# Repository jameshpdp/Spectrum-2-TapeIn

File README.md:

# ZX Spectrum +2 (Grey) External Tape Input PCB

This is a simple PCB layout for building circuit designed by
[JoulesperCoulomb](https://youtu.be/qUIv-A_DOc0?t=1213), please
watch the video for all the details.

Board size 40mm x 30mm. Gerber files under `export/`, original KiCad project under
`Spectrum+2-TapeIn.KiCad/`.

## Building

Building this circuit shold be straghtforward with one exception. It is recommended to solder wires directly to the PCB1 pads and avoid using pin header there.

NOTE: While PCB1 connector footprint allows for soldering KK 254 / KF 2510  pin header, great care should be taken to solder those correctly. The problem is not the pin header itself, but the cable you need to use to connect it to the main board. Most pre-crimped cables available at the time of writing (2023) are the cross-wired ones (pin 1 to 5, pin 2 to 4, pin 4 to 2, pin 5 to 1). Which means if you do not pay attention you may end up cross-connecting MIC and EAR. At best, nothing will work. At worst, you may damage that precious ULA. Just get the wires with the KK 254 / KF 2510 connector on one end and carefully solder wires according to the skilscreen markings.

[Interactive BOM](https://htmlpreview.github.io/?https://github.com/jameshpdp/Spectrum-2-TapeIn/blob/main/bom/ibom.html)

| Reference         | Item     | Count |
| ----------------- | -------- | ----- |
| C1, C2            | 20 nF    |     2 |
| C3                | 22 uF    |     1 |
| R1-R4, R6, R7, R9 | 100 kOhm |     7 |
| R5                | 470 kOhm |     1 |
| R8                | 68 kOhm  |     1 |
| D2            | 1N5819   |     1 |
| U1                | LM358    |     1 |
| DECK1, PCB1 (opt) | Molex KK-254 AE-6410 | 1 (2) |

Molex KK 254 / KF 2510 connectors optional, required only if you want to avoid cutting/modifing existing tape deck wiring. Otherwise you can simply solder wires to the corresponding pads as marked on the PCB.

## Revision Hisory
Rev. C -- first public release

Rev. D -- KK 254 / 2510 connectors (optional), removed D1, extra details on the silkscreen

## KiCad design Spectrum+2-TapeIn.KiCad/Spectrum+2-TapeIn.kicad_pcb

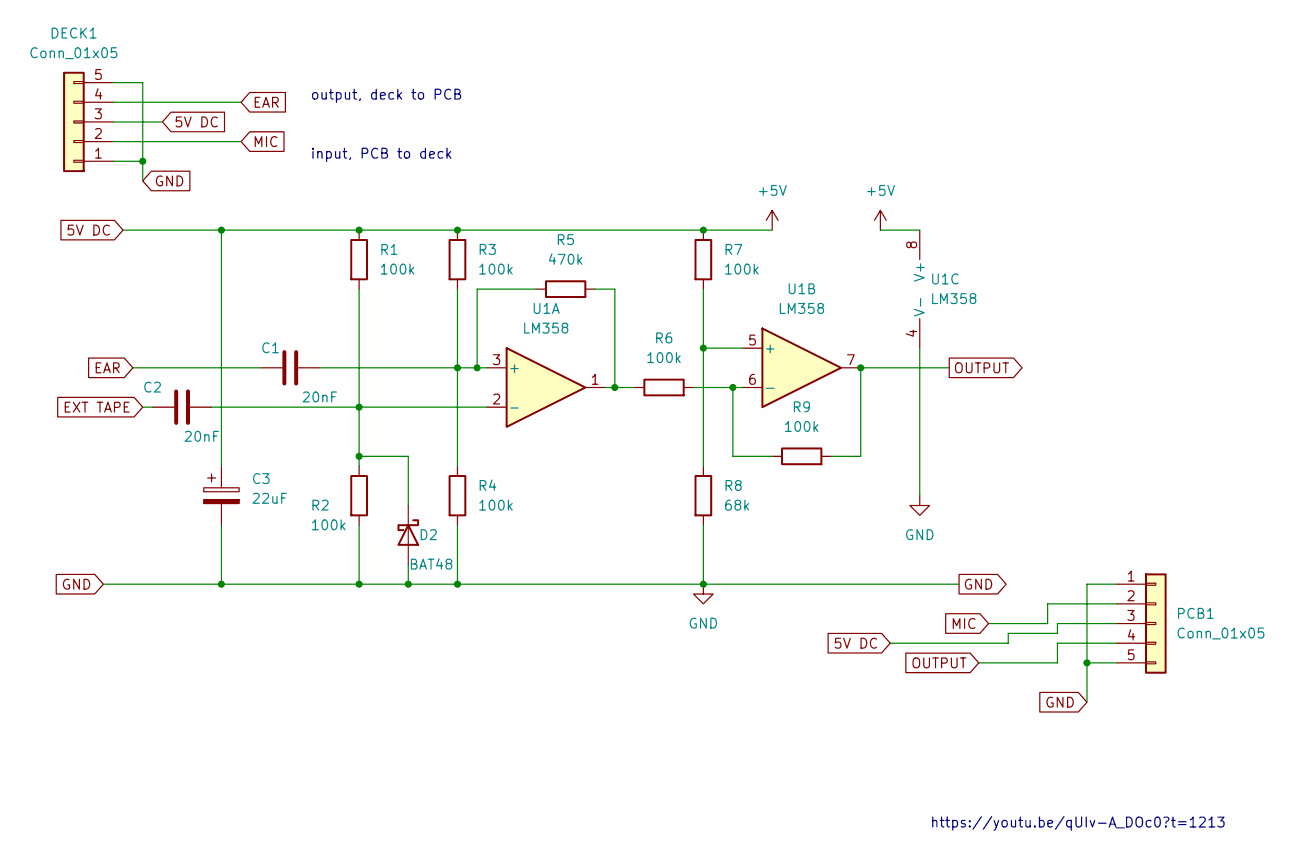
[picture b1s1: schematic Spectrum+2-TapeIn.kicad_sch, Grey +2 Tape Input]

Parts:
C1, C2: 20nF; C_Disc_D5.1mm_W3.2mm_P5.00mm; Part Number K223K15X7RF53L2
C3: 22uF; CP_Radial_D5.0mm_P2.00mm; Part Number ECA1CM220
D2: BAT48; D_A-405_P10.16mm_Horizontal; Part Number BAT48RL
DECK1: Conn_01x05; Molex_KK-254_AE-6410-05A_1x05_P2.54mm_Vertical
PCB1: Conn_01x05; Molex_KK-254_AE-6410-06A_1x05_P2.54mm_Vertical
R1, R2, R3, R4, R6, R7, R9: 100k; R_Axial_DIN0207_L6.3mm_D2.5mm_P10.16mm_Horizontal; Part Number 100k 0.25W
R5: 470k; R_Axial_DIN0207_L6.3mm_D2.5mm_P10.16mm_Horizontal; Part Number 470k 0.25W
R8: 68k; R_Axial_DIN0207_L6.3mm_D2.5mm_P10.16mm_Horizontal; Part Number 68k 0.25W
U1: LM358; DIP-8_W7.62mm; Part Number LM358

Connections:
5V DC: C3.1, DECK1.3, PCB1.3, R1.1, R3.1, R7.1, U1.8 (V+)
EAR: C1.1, DECK1.4
EXT TAPE: C2.1; also elsewhere on the board
GND: C3.2, D2.2 (A), DECK1.1, DECK1.5, PCB1.1, PCB1.5, R2.2, R4.2, R8.2, U1.4 (V-); also elsewhere on the board
MIC: DECK1.2, PCB1.2
unnamed: C2.2, D2.1 (K), R1.2, R2.1, U1.2 (-)
unnamed: R5.2, R6.1, U1.1
unnamed: C1.2, R3.2, R4.1, R5.1, U1.3 (+)
unnamed: R7.2, R8.1, U1.5 (+)
unnamed: R6.2, R9.1, U1.6 (-)
OUTPUT: PCB1.4, R9.2, U1.7

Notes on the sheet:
input, PCB to deck
output, deck to PCB
https://youtu.be/qUIv-A_DOc0?t=1213

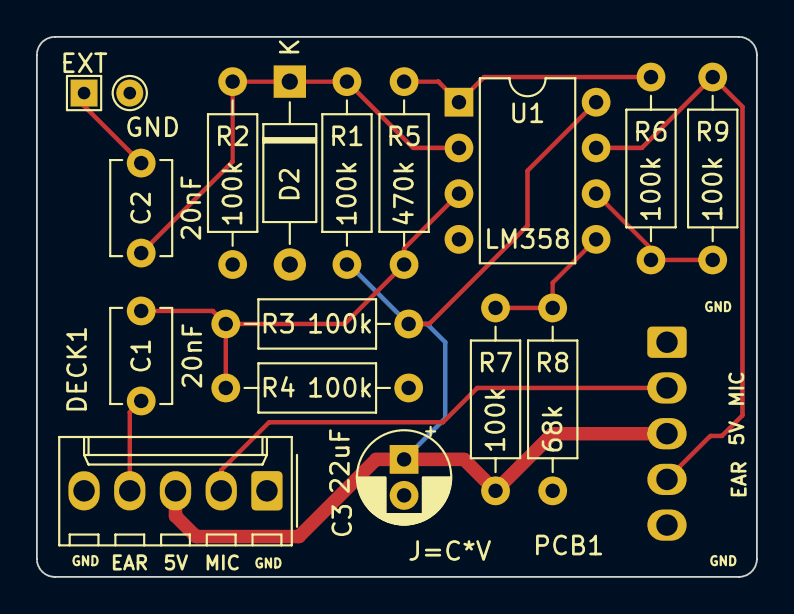
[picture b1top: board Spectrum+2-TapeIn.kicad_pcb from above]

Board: 2 copper layers, 40.0 x 30.0 mm, 18 parts (0 on the bottom side), 11 nets.

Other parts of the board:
EXT: TestPoint_THTPad_1.5x1.5mm_Drill0.7mm
GND: TestPoint_THTPad_D1.5mm_Drill0.7mm

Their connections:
EXT TAPE: EXT.1; also elsewhere on the board
GND: GND.1; also elsewhere on the board

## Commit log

2023-10-19 Initial import
2023-11-14 Rev. D
    Proper connector for deck plug (no need to cut the wires).
    Improved silkscreen, makes it easier to place components when building.
2023-11-14 Typo, preview link.
    Typo, pin does not respond to a ping :) Preview link for BOM page.
